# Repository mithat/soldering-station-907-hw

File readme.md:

Soldering Station 907
---------------------

Mithat Konar

A PCB implementation for [sfrwmaker/soldering_907_lcd
](https://github.com/sfrwmaker/soldering_907_lcd) using a 1602 LCD.

Note: After starting this, I discovered that the supply of decent 907-style handles has really dried up. So I'm probably going to leave this unfinished and instead do what all the cool kids are doing and move to something using a T12-style handle.

---------------------------------

I've tried to keep as close to sfrwmaker's original schematic as possible, but I made some changes to reflect best practices. In particular:

* I've added some additional 0.1u bypass capacitors.
* All the buzzers I looked at drew current that was uncomfortably close or exceeded the ATmega328p's absolute maximum of 40mA. So I adopted an easy to source (in the USA, anyway) buzzer (without internal oscillator) and added a driver circuit that offloads the Nano.

Some notes:
* Symbols that aren't found in the default KiCad 5.x distributions are in `local.lib`. Footprints not found in the default KiCad 5.x distributions are in `local.pretty`. If KiCad barks at you about missing things, add these to the project using the respective symbol and footprint managers.
* A custom Arduino Nano symbol was needed to make the design pass DRC. Specifically, the +5V power output pin was made a power input to reflect how that pin is being used here.
* Something better suited to the design than the inexpensive eBay [LM2596 DC-DC module](https://www.ebay.com/itm/10-PCS-LM2596-DC-DC-buck-adjustable-step-down-Power-Supply-Converter-module-/221920170517?hash=item33ab791215:g:5zEAAOSw~bFWKKJO) is very likely, but I used this because the original designer did so  in their [Hackster.io project](https://www.hackster.io/sfrwmaker/soldering-iron-controller-for-hakko-907-v-2-fc75d7). **The footprint for this part is currently not correct.** The outer dimensions were taken from an eBay posting, and the pad and mounting hole locations and sizes are wild guesses from images.
* Better alternatives to the MCP602 (and AD822) are probably available, but again I am sticking as much as possible to the original design.

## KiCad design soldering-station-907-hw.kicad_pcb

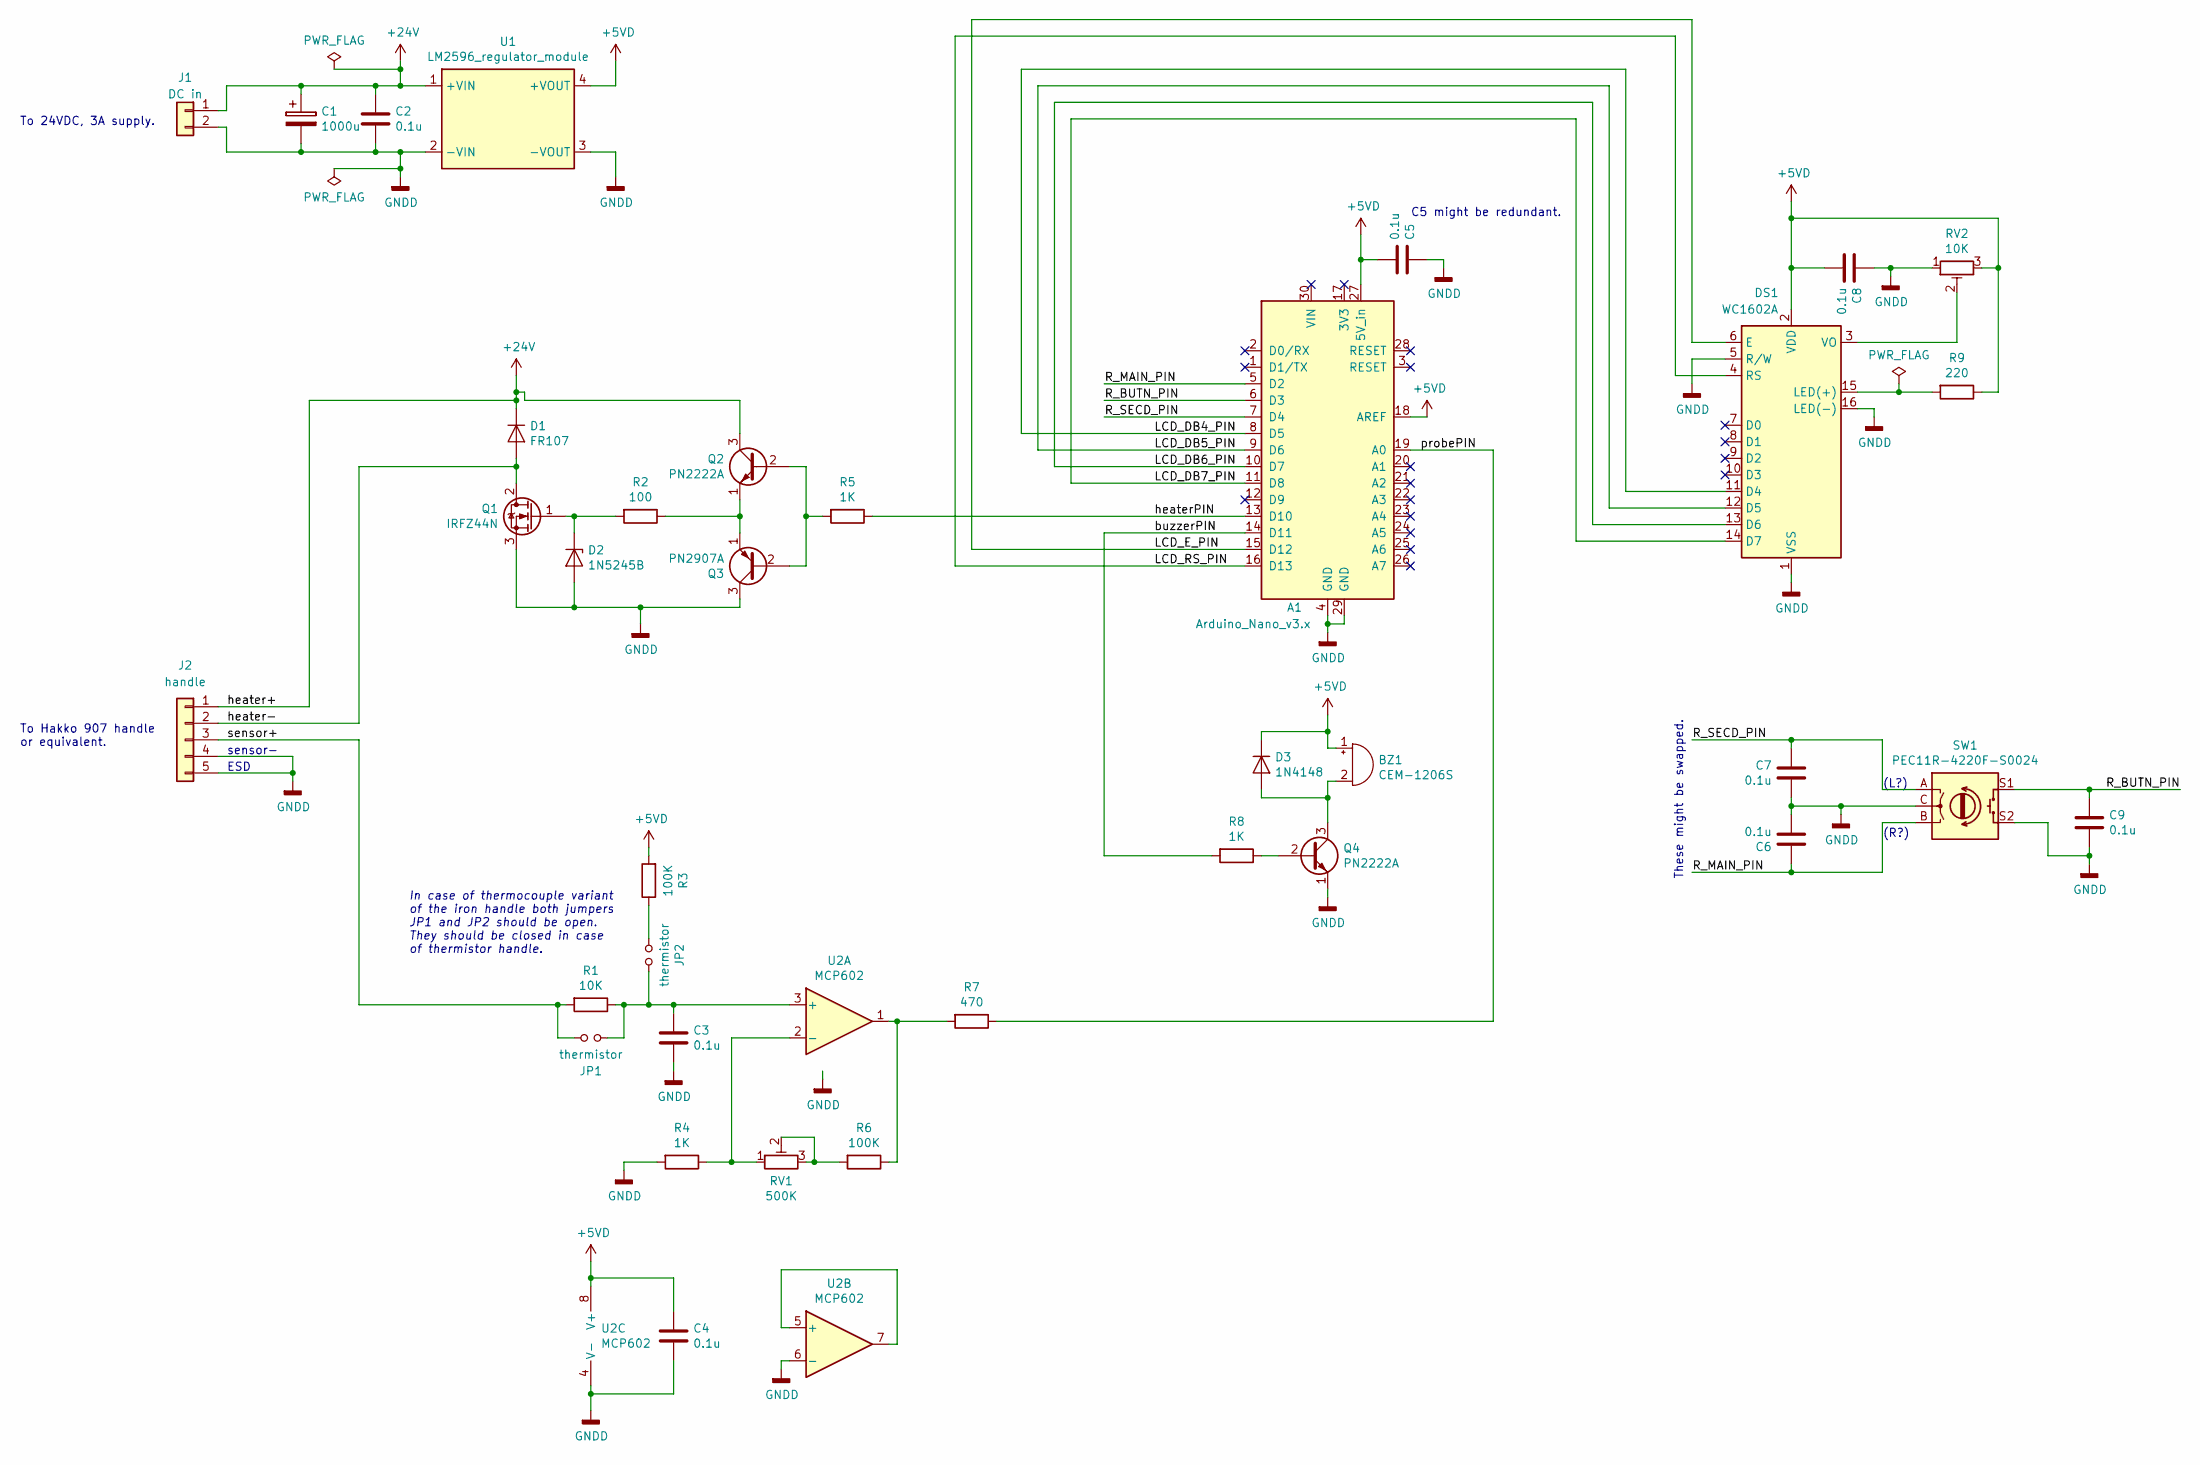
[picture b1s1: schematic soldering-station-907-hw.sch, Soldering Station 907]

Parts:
A1: Arduino_Nano_v3.x; Arduino_Nano_WithMountingHoles
BZ1: CEM-1206S; MagneticBuzzer_ProSignal_ABT-410-RC
C1: 1000u; CP_Radial_D12.5mm_P5.00mm
C2, C3, C4, C5, C6, C7, C8, C9: 0.1u; C_Rect_L4.0mm_W2.5mm_P2.50mm
D1: FR107; D_DO-41_SOD81_P10.16mm_Horizontal
D2: 1N5245B; D_DO-35_SOD27_P7.62mm_Horizontal
D3: 1N4148; D_DO-35_SOD27_P7.62mm_Horizontal
DS1: WC1602A
J1: DC in; JST_VH_B2P-VH-FB-B_1x02_P3.96mm_Vertical
J2: handle; JST_VH_B5P-VH-FB-B_1x05_P3.96mm_Vertical
JP1, JP2: thermistor; PinHeader_1x02_P2.54mm_Vertical
Q1: IRFZ44N; TO-220-3_Vertical
Q2, Q4: PN2222A; TO-92_HandSolder
Q3: PN2907A; TO-92_HandSolder
R1: 10K; R_Axial_DIN0207_L6.3mm_D2.5mm_P10.16mm_Horizontal
R2: 100; R_Axial_DIN0207_L6.3mm_D2.5mm_P10.16mm_Horizontal
R3, R6: 100K; R_Axial_DIN0207_L6.3mm_D2.5mm_P10.16mm_Horizontal
R4, R5, R8: 1K; R_Axial_DIN0207_L6.3mm_D2.5mm_P10.16mm_Horizontal
R7: 470; R_Axial_DIN0207_L6.3mm_D2.5mm_P10.16mm_Horizontal
R9: 220; R_Axial_DIN0207_L6.3mm_D2.5mm_P10.16mm_Horizontal
RV1: 500K; Potentiometer_Bourns_3296W_Vertical
RV2: 10K; Potentiometer_Bourns_3386F_Vertical
SW1: PEC11R-4220F-S0024; RotaryEncoder_Alps_EC12E-Switch_Vertical_H20mm
U1: LM2596_regulator_module
U2: MCP602; DIP-8_W7.62mm_Socket_LongPads

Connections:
+5VD: A1.18 (AREF), A1.27 (5V_in), BZ1.1 (-), C4.1, C5.2, C8.2, D3.1 (K), DS1.2 (VDD), R3.2, R9.1, RV2.3, U1.4 (+VOUT), U2.8 (V+)
+24V: C1.1, C2.1, D1.1 (K), J1.1, J2.1, Q2.3 (C), U1.1 (+VIN)
/LCD_DB4_PIN: A1.8 (D5), DS1.11 (D4)
/LCD_DB5_PIN: A1.9 (D6), DS1.12 (D5)
/LCD_DB6_PIN: A1.10 (D7), DS1.13 (D6)
/LCD_DB7_PIN: A1.11 (D8), DS1.14 (D7)
/LCD_E_PIN: A1.15 (D12), DS1.6 (E)
/LCD_RS_PIN: A1.16 (D13), DS1.4 (RS)
/R_BUTN_PIN: A1.6 (D3), C9.1, SW1.S1
/R_MAIN_PIN: A1.5 (D2), C6.1, SW1.B
/R_SECD_PIN: A1.7 (D4), C7.1, SW1.A
/buzzerPIN: A1.14 (D11), R8.2
/heater-: D1.2 (A), J2.2, Q1.2 (D)
/heaterPIN: A1.13 (D10), R5.1
/probePIN: A1.19 (A0), R7.1
/sensor+: J2.3, JP1.1, R1.2
GNDD: A1.4 (GND), A1.29 (GND), C1.2, C2.2, C3.2, C4.2, C5.1, C6.2, C7.2, C8.1, C9.2, D2.2 (A), DS1.1 (VSS), DS1.5 (R/W), DS1.16 (LED(-)), J1.2, J2.4, J2.5, Q1.3 (S), Q3.3 (C), Q4.1 (E), R4.2, RV2.1, SW1.C, SW1.S2, U1.2 (-VIN), U1.3 (-VOUT), U2.4 (V-), U2.6 (-)
unnamed: BZ1.2 (+), D3.2 (A), Q4.3 (C)
unnamed: C3.1, JP1.2, JP2.2, R1.1, U2.3 (+)
unnamed: D2.1 (K), Q1.1 (G), R2.2
unnamed: DS1.3 (VO), RV2.2
unnamed: DS1.15 (LED(+)), R9.2
unnamed: JP2.1, R3.1
unnamed: Q2.1 (E), Q3.1 (E), R2.1
unnamed: Q2.2 (B), Q3.2 (B), R5.2
unnamed: Q4.2 (B), R8.1
unnamed: R4.1, RV1.1, U2.2 (-)
unnamed: R6.1, R7.2, U2.1
unnamed: R6.2, RV1.2, RV1.3
unnamed: U2.5 (+), U2.7

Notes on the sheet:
These might be swapped.
In case of thermocouple variant of the iron handle both jumpers JP1 and JP2 should be open. They should be closed in case of thermistor handle.
sensor-
ESD
To Hakko 907 handle or equivalent.
To 24VDC, 3A supply.
C5 might be redundant.
(R?)
(L?)

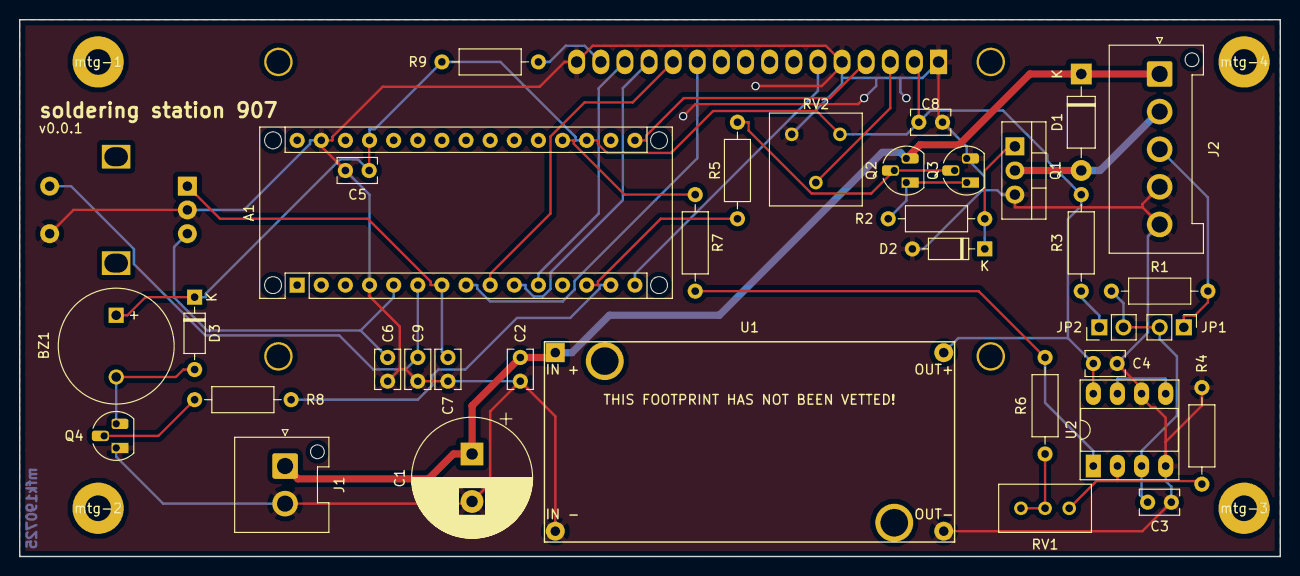
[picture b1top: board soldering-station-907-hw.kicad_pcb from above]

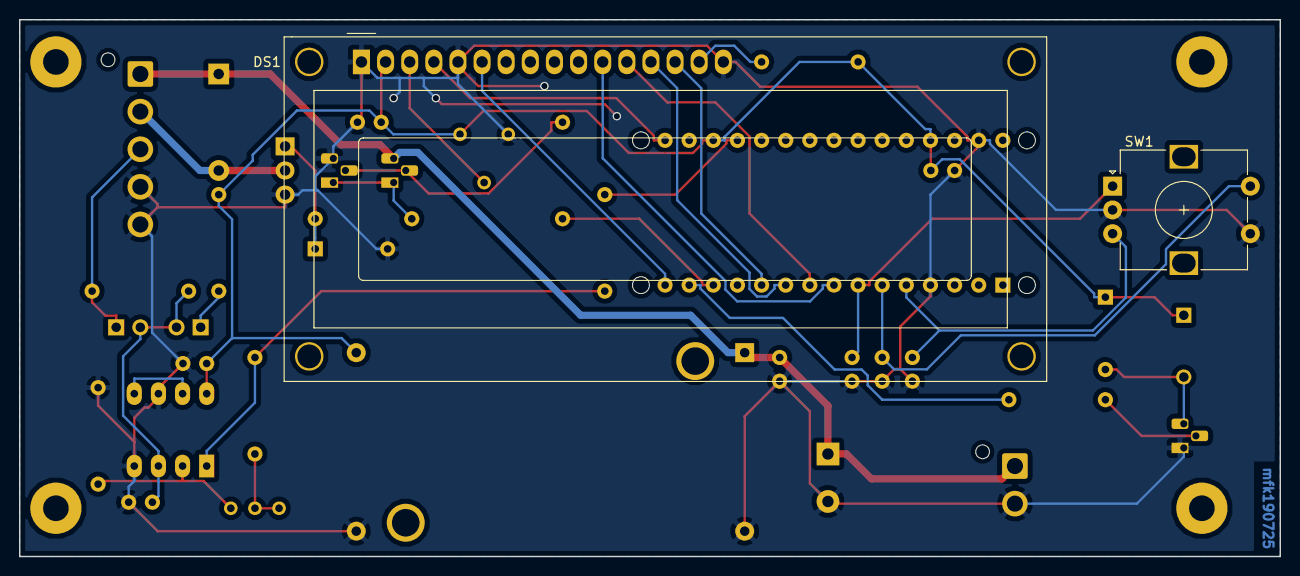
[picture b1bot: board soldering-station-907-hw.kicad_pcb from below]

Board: 2 copper layers, 132.7 x 56.5 mm, 41 parts (2 on the bottom side), 30 nets.

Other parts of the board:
mtg-1, mtg-2, mtg-3, mtg-4: MountingHole_2.7mm_M2.5_Pad

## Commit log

2019-07-25 Initial commit. Schematic complete.
2019-07-25 Parts placed.
2019-07-25 Routed.
2019-07-25 Copper pours.
2019-07-25 Silkscreen label.
2019-07-25 Readme bump.
2019-07-25 Swapped R/L pins of SW1. Moved RV1 to front of board. Routing tweaks.
2019-07-25 Readme tweaks.
